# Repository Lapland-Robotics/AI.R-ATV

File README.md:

# AI.R-Autonomous_Robot

This is a modular, ROS2‑based platform designed to streamline the development and deployment of autonomous mobile robots. At its core, it leverages ROS2 Navigation 2 for robust path planning and obstacle avoidance, integrates a flexible sensor suite (Lidar, Stereo camera, Thermal camera, GNSS module, ultrasonic array) for reliable perception, and employs Docker containers to ensure reproducible builds. From low‑level firmware on ESP32 microcontrollers to high‑level controls on an NVIDIA Jetson.

## Directory Tree view
This section outlines the main directory structure of the project, separating documents, firmware, hardware designs, and ROS2-based software to keep development organized and modular.
```

├── Documents           # All the Documents and Diagrams
│   ├── MiniATV         # Documents about mini ATV
│   └── Snower          # Documents about Snower
├── Firmware            # All the Firmware programs (for Micro controllers)
├── Hardware            # Universal PCB Design and implementation
├── README.md           # main README file
└── Software            # ROS2 project for Main Brain(Jetson) of the Robots 

```

## System Overview

## ROS2 Transformation Frame Hierarchy

The robot uses a structured TF (transform) tree to manage spatial relationships between all its components, including sensors, base links, and actuators. This hierarchy ensures that data from various sources—like lidar, camera, and GNSS—can be accurately fused and interpreted in a common coordinate space. The TF tree below visualizes how frames are connected and updated in real time during operation.

## Robot Node & Topic Architecture

The ROS2 system is composed of multiple nodes that communicate through a network of topics to handle various tasks like localization, navigation, perception, and control. Each node is modular and focused on a specific function

This diagram, generated with `rqt_graph`, illustrates the live connections between all ROS2 nodes and topics in the Snower. It shows how sensor publishers (e.g., lidar, camera, GNSS, odometry) feed into processing and filtering nodes, how planners and behavior servers interact via action servers/topics, and how control commands flow down to the motor drivers and micro-ROS bridge on the ESP32. By visualizing the full publisher–subscriber and action-server network, you can more verify how each node is wired into the overall autonomy pipeline.

#### In this video, we are testing the autonomous waypoint navigation and dynamic obstacle avoidance capabilities of the Snower 

Click the thumbnail below to watch the demo video:

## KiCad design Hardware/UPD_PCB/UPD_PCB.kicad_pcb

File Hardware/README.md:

# HARDWARE
This folder contains all hardware-related documentation, schematics, PCB designs, and data collection tools for the autonomous robot system.

# Directory Tree view
This section outlines the structure of the Hardware directory, which contains PCB designs, electrical schematics, component research, data logging utilities, and comprehensive documentation for the robot's power distribution and monitoring systems.

```
├── Data_logging                # Python scripts and Excel files for sensor data collection
├── PCB_research                # Research documentation and testing for PCB components
├── UPD_PCB                     # Universal Power Distribution PCB design files
└── User_Manual-UPD-PCB.pdf     # Comprehensive user manual for the UPD PCB
```
# Universal Power Distribution PCB

Designed and developed by Dries Nuttin

## Introduction

The Universal Power Distribution PCB (UDP-PCB) provides the possibility for quick and easy power distribution in any robotics or electronics project ensuring maximum efficiency. A single battery can provide power to 6 different voltage rails with their respective voltage levels (24V, 19V, 16V, 12V, 12V, 5V). Each stage can supply up to 3.5 Amps continuously with a max voltage input of 60V.

A separate battery output has been provided to allow for a motor driver input equal to the battery voltage, protected by a switchable fuse for easier integration into any project. Each voltage rail (except the battery output) has its own INA219 current/voltage/power sensor that communicates via I²C. The current of the entire system is monitored by an ACS711 HALL sensor which sends out a voltage in relation to the current delivered by the battery. An onboard STS30 digital temperature sensor supplies the user with real-time temperature data to ensure that the PCB/ambient temperature does not reach self-made limits.

### Key Features

- **7 voltage outputs** (BAT+, 24V, 19V, 16V, 12V, 12V, 5V)
- **Single battery input** of 4.3V to 60V max
- **6 different voltages** from 1 battery input
- **±1% voltage level accuracy**
- **3.5 Amps continuous**, with a maximum pulse current of 4.3 Amps
- **Real-time monitoring** of current/voltage/power for 6 voltage rails
- **Real-time HAL current monitoring** of the entire current consumption of the PCB
- **Real-time temperature monitoring**
- **Main system over current fault indicator**
- **Rail supply malfunction indicator**
- **±85% Efficiency** for each buck converter stage
- **BAT+ Fuse protection**
- **Single rail shutdown** that leaves the rest unaffected
- **Over current / temperature protection** on each rail
- **No Over-voltage protection**

> **Note:** V1.0 still has specific repair requirements in place, please consult the repair section of the Hardware/User_Manual-UPD-PCB.pdf to see what needs to be done for newly purchased PCBs.

## Product Specifications

### Absolute Maximum Ratings

| No. | Parameter | Min | Typical | Max | Unit |
|-----|-----------|-----|---------|-----|------|
| 1 | Input voltage (Battery+) | 4.3 | - | 60 | V |
| 2 | Current Battery input (Continuous) |  | 32 |   | A |
| 3 | Current Battery input (1 pulse, 100ms) |   | 100 |   | A |
| 4 | Rail current (Continuous) |   | 3.5 |   | A |
| 5 | Rail current (pulsed, hiccup mode) |   | 6 |   | A |
| 6 | Current usage with no output |   | 54 |   | mA |
| 7 | Thermal shutdown threshold |   | 165 |   | °C |
| 8 | PCB temperature | -40 | 35 | 165 | °C |

> **Warning:** These ratings should not be exceeded, doing so can lead to permanent damage to the PCB or components.

### Pin Configuration

| Label | Function | Description |
|-------|----------|-------------|
| A | Main battery input | 4.2V to 60V |
| B | Fuse | Linked to output E |
| C | ACS711 VIout output | Current sensor output |
| D | I²C output | Sensor communication |
| E | Main battery output | With fuse protection |
| F | 24V output | Regulated 24V rail |
| G | 19V output | Regulated 19V rail |
| H | 16V output | Regulated 16V rail |
| I | 12V_1 output | First 12V rail |
| J | 12V_2 output | Second 12V rail |
| K | 5V output | Regulated 5V rail |

**Color Legend:**
- Red = Power input/output
- Yellow = Sensor output
- Grey = Fuse

### LED Status Indicators

If all LEDs are on = Working as expected

| Label | Function | Meaning if not on |
|-------|----------|-------------------|
| A | Fault for ACS711 HALL current sensor | Overcurrent |
| B | Battery output voltage line | No voltage available |
| C | 24V output voltage line | No voltage available |
| D | 19V output voltage line | No voltage available |
| E | 16V output voltage line | No voltage available |
| F | 12V output voltage line | No voltage available |
| G | 12V output voltage line | No voltage available |
| H | 5V output voltage line | No voltage available |

> **Note:** The described reasons might not be the only reasons that the LED is off. The LED itself might be broken, the voltage might be unstable, a connection might have severed, the LED resistor might have broken. Please test the power supplies with multimeter. If the LED is off, please consult the repair section of the Hardware/User_Manual-UPD-PCB.pdf.

## How to Use

The UPD-PCB can be utilized in any robotics project that is powered by 1 battery. This battery can be plugged into the PCB, which will follow by the indicator LEDs turning on and each stage delivering an output voltage. Screw terminals have been provided for ease of use to attach the necessary voltage lines. The GND is shared between all terminals, meaning you can switch the ground cables between voltage in/outputs even though this is not recommended.

### Integration Checklist

To integrate the UPD-PCB into any robotics project please ensure the following:

- The battery output is correctly plugged into the screw terminal plug on the PCB
- It is recommended to have a battery switch and anti-spark unit before the PCB
- The Fuse is plugged into the PCB if battery output is required
- All LEDs are on
- The output wires have the correct polarity
- If needed, the I²C and VIout connections are plugged into an external MCU unit

### Example Setup

An example of a UPD-PCB plugged in correctly. Note that the LEDs are not on due to the battery being switched off.

As can be seen in the image, the polarity of the wires is ensured and coherent with the silkscreen on the PCB itself. The fuse is in place for, in this specific case, 25A, and the I²C and VIout wires are not connected. If the battery was enabled, the LEDs should light up and the PCB will immediately work without issue.

> **Note:** The sensors do not need to be enabled for the PCB to deliver stable power

> **Warning:** It is not recommended to plug/unplug any wires while the PCB is on. Doing so can result in permanent damage if any of the live wires touch the IC's or a spark is generated.

## Power Delivery

The power delivery for each rail is being supplied by a fine-tuned LMR516x5 buck converter. This buck converter works at 400 kHz (might vary due to the FPM version being utilized in this design). More information can be found in the datasheet of the buck converter itself. Each buck converter has been chosen for its high efficiency, low thermal rise, high power output (3.5A continuous).

### Voltage Setting

The output voltage of each rail is decided using an external resistor. This resistor is visible in the image above where the resistor R3 has a red square surrounding it. If the output voltage needs to be replaced or is not at the desired resistance, please change this resistor.

The desired resistor value can be calculated using this equation. All resistors used are size 0603.

```
Resistor = (Vout - 0.8V) / 0.8V × 10200
```

## Sensor Integration

The UPD-PCB can monitor each individual rail for voltage, current and power usage. This can be done by a single MCU which has to read out 1 I²C bus and read out an ADC voltage signal. By following the steps in this section, you will be able to read out these sensors and use them for any application.

An example of the sensor integration. Here you can see an ESP32 actively reading out both the VIout pin and the I²C line from the entire PCB.

### INA219

All relevant I²C addresses can be found in the table below. These addresses are changeable if the A1 and A0 connections are changed. Please note that the I²C address for the temperature sensor is identical to the 16V line (0x4A), this table below already has the changed I²C address, the change itself can be found in the repair section of the Hardware/User_Manual-UPD-PCB.pdf.

| Voltage | A1 Connection | A0 Connection | I²C Address (Binary) | I²C Address (Hex) |
|---------|---------------|---------------|---------------------|-------------------|
| +24V | GND | GND | 1000000 | 0x40 |
| +19V | GND | +5V | 1000001 | 0x41 |
| +16V | GND | SDA | 1000010 | 0x42 |
| +12V_1 | +5V | GND | 1000100 | 0x44 |
| +12V_2 | +5V | +5V | 1000111 | 0x47 |
| +5V | +5V | SDA | 1000101 | 0x45 |

#### Arduino Code

Programming a MCU to receive INA219 data from the UPD-PCB can be done using the Arduino IDE:

1. Open the Arduino library manager
2. Search for the Adafruit INA219 library and install it
3. With this, one of the examples can be opened and it should be ready to use!
4. Ensure that you are using one of the addresses previously mentioned in order to read out from the correct sensor.

More information regarding the INA219 can be found [here](https://cdn-learn.adafruit.com/downloads/pdf/adafruit-ina219-current-sensor-breakout.pdf).

Example code for selecting the correct address:

```cpp
#include <Wire.h>
#include <Adafruit_INA219.h>

Adafruit_INA219 ina219(0x41); // 0x41 = +19V line

void setup() {
  Serial.begin(9600);
  ina219.begin();
}

void loop() {
  Serial.print("V: "); Serial.print(ina219.getBusVoltage_V());
  Serial.print("V, I: "); Serial.print(ina219.getCurrent_mA());
  Serial.print("mA, P: "); Serial.print(ina219.getPower_mW());
  Serial.println("mW");
  delay(1000);
}
```

### ACS711

The ACS711 is a Hall-effect-based current sensor that outputs an analog voltage proportional to the current passing through the entire system. It can be connected to an MCU's ADC pin to allow for full-system current monitoring.

**Specifications:**
- Output voltage (VIout) at 0A: VCC / 2 = 2.5V
- Sensitivity: ~45 mV per Amp
- Range: 30A

A calculation must be made in the MCU to determine the correct amount of current. Since the baseline for the ACS is half of the supply voltage (5V) and any positive current will simply add 0.045V/A on top of that baseline. If the current goes in reverse (which it should never do) the VIout will go lower.

The following calculation can be made:

```
Current (A) = (Vout - 5V/2) / 0.045V
```

Example code implementation:

```cpp
const int ACS_PIN = 36; // e.g., GPIO36 (ADC1)

void setup() {
  Serial.begin(9600);
}

void loop() {
  int adc = analogRead(ACS_PIN);
  float voltage = adc * 5.0 / 4095.0;
  float current = (voltage - 2.5) / 0.045; // 45mV per Amp
  
  Serial.print("Current: "); Serial.print(current); Serial.println(" A");
  delay(1000);
}
```

> **Note:** The 16V INA219 sensor has the same I²C address as the Temperature sensor before doing any repairs. Ensure that you either follow the steps in the repair section of the Hardware/User_Manual-UPD-PCB.pdf, or don't use the temperature sensor.

> **Best Practice:** The best way to ensure accurate measurement is to read out the 5V line from the INA219 sensor and use that in the calculation for the supply voltage. Replace 5V with the correct voltage measurement.

### STS30

The STS30 is a digital I²C temperature sensor made by Sensirion, known for its high accuracy and reliability. It outputs temperature values in °C directly over the I²C bus.

**Specifications:**
- Communication: I²C
- I²C address: 0x4A
- Accuracy: ±0.2°C
- Range: -40°C to +125°C

To read out the temperature sensor, an Arduino library such as SHT31 can be used to make it easier to read out the temperature sensor.

```cpp
#include <Wire.h>
#include "Adafruit_SHT31.h"

Adafruit_SHT31 sht = Adafruit_SHT31();

void setup() {
  Serial.begin(9600);
}

void loop() {
  float temp = sht.readTemperature();
  if (!isnan(temp)) {
    Serial.print("Temperature: ");
    Serial.print(temp);
    Serial.println(" °C");
  }
  delay(1000);
}
```

### For more information, please refer to the Hardware/User_Manual-UPD-PCB.pdf.

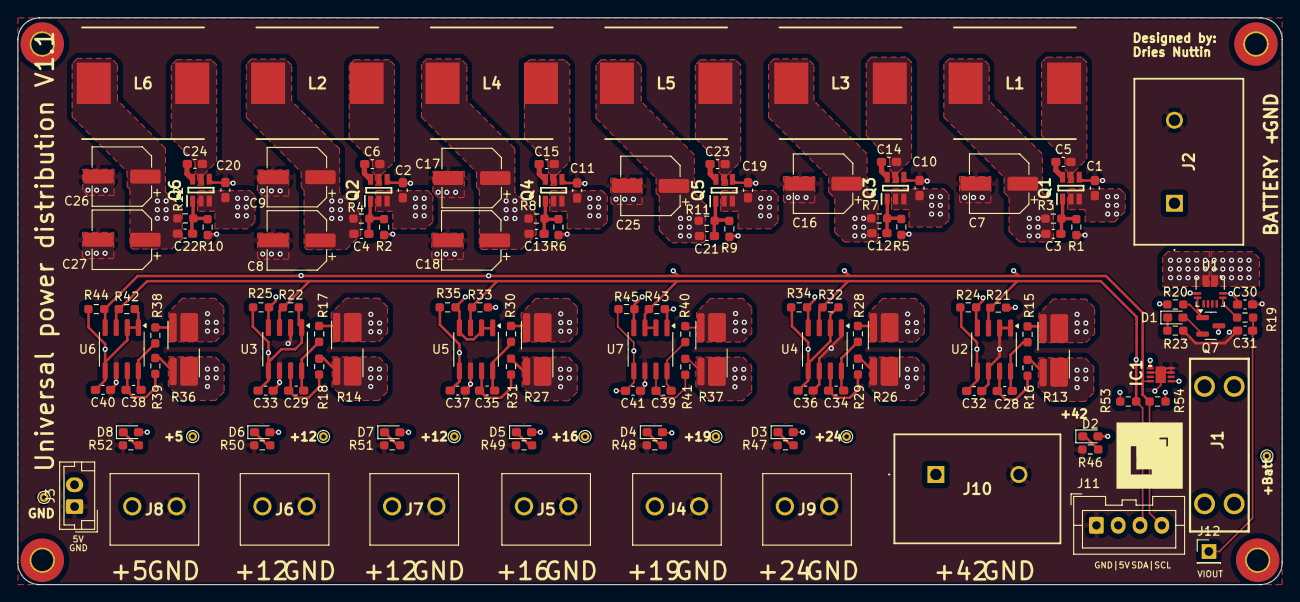
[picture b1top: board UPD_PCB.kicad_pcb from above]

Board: 6 copper layers, 145.0 x 65.0 mm, 144 parts (0 on the bottom side), 60 nets.

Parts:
C1, C2, C10, C11, C19, C20: 2.2µF; C_0603_1608Metric_Pad1.08x0.95mm_HandSolder
C3, C4, C12, C13, C21, C22: DNP; C_0603_1608Metric_Pad1.08x0.95mm_HandSolder
C5, C6, C14, C15, C23, C24, C28, C29, C30, C31, C32, C33, C34, C35, C36, C37, C38, C39, C40, C41: 0.1µF; C_0603_1608Metric_Pad1.08x0.95mm_HandSolder
C7, C9, C16, C18, C25: 22µF; CP_Elec_6.3x5.8
C8, C17: 10µF; CP_Elec_6.3x5.8
C26, C27: 33µF; CP_Elec_6.3x5.8
D1, D2, D3, D4, D5, D6, D7, D8: LED; LED_0603_1608Metric_Pad1.05x0.95mm_HandSolder
IC1: STS30-DIS; SON50P250X250X100-9N-D
J1: 25A Fuse holder; 3557-2
J2, J10: 796739-2; 7967392
J3: Conn_01x02; JST_EH_B2B-EH-A_1x02_P2.50mm_Vertical
J4, J5, J6, J7, J8, J9: 1776119-2; 17761192
J11: Conn_01x04; JST_XA_B04B-XASK-1_1x04_P2.50mm_Vertical
J12: Conn_01x01; PinHeader_1x01_P2.54mm_Vertical
L1, L3, L5: 33µH; INDPM140128X650N
L2, L4: 22µH; INDPM140128X650N
L6: 15µH; INDPM140128X650N
Q1, Q2, Q3, Q4, Q5, Q6: LMR51635XDDCR; SOT95P280X110-6N
Q7: BSS84; SOT-23
R1, R2, R5, R6, R9, R10: 10k2; R_0603_1608Metric_Pad0.98x0.95mm_HandSolder
R3: 295k; R_0603_1608Metric_Pad0.98x0.95mm_HandSolder
R4, R8: 143k; R_0603_1608Metric_Pad0.98x0.95mm_HandSolder
R7: 232k; R_0603_1608Metric_Pad0.98x0.95mm_HandSolder
R11: 194k; R_0603_1608Metric_Pad0.98x0.95mm_HandSolder
R12: 53k5; R_0603_1608Metric_Pad0.98x0.95mm_HandSolder
R13, R14, R26, R27, R36, R37: 0.1R; R_shunt_different_pad_layout
R15, R16, R17, R18, R28, R29, R30, R31, R38, R39, R40, R41: R50; R_0603_1608Metric_Pad0.98x0.95mm_HandSolder
R19: 0R; R_0603_1608Metric_Pad0.98x0.95mm_HandSolder
R20, R50: 1k; R_0603_1608Metric_Pad0.98x0.95mm_HandSolder
R21, R22, R24, R25, R32, R33, R34, R35, R42, R43, R44, R45, R53, R54: 10k; R_0603_1608Metric_Pad0.98x0.95mm_HandSolder
R23, R51, R52: 330; R_0603_1608Metric_Pad0.98x0.95mm_HandSolder
R46: 4k; R_0603_1608Metric_Pad0.98x0.95mm_HandSolder
R47: 2.2k; R_0603_1608Metric_Pad0.98x0.95mm_HandSolder
R48: 1.8k; R_0603_1608Metric_Pad0.98x0.95mm_HandSolder
R49: 1.4k; R_0603_1608Metric_Pad0.98x0.95mm_HandSolder
TP1, TP2, TP3, TP4, TP5, TP6, TP7, TP8: TestPoint; TestPoint_THTPad_D1.0mm_Drill0.5mm
U1: ACS711xEXLT-31AB; Allegro_QFN-12-10-1EP_3x3mm_P0.5mm
U2, U3, U4, U5, U6, U7: INA219AxD; SOIC-8_3.9x4.9mm_P1.27mm

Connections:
+5V_NS: C22.2, C26.1, C27.1, L6.2, R12.1, R36.1, R36.2, R38.1
+5V_out: C30.1, C32.2, C33.2, C36.2, C37.2, C40.2, C41.2, D8.2 (A), IC1.5 (VDD), J3.2, J8.1, J11.2, Q7.3 (D), R20.1, R21.2, R22.2, R24.2, R25.2, R32.2, R33.2, R34.2, R35.2, R36.3, R36.4, R39.1, R42.2, R43.2, R44.2, R45.2, R53.2, R54.2, TP7.1, U1.10 (VCC), U2.5 (VS), U3.1 (A1), U3.5 (VS), U4.2 (A0), U4.5 (VS), U5.5 (VS), U6.1 (A1), U6.2 (A0), U6.5 (VS), U7.1 (A1), U7.5 (VS)
+12V_1: C4.2, C8.1, C9.1, L2.2, R4.1, R14.1, R14.2, R17.1
+12V_1_out: D6.2 (A), J6.1, R14.3, R14.4, R18.1, TP3.1
+12V_2: C13.2, C17.1, C18.1, L4.2, R8.1, R27.1, R27.2, R30.1
+12V_2_out: D7.2 (A), J7.1, R27.3, R27.4, R31.1, TP5.1
+16V: C21.2, C25.1, L5.2, R11.1, R37.1, R37.2, R40.1
+16V_out: D5.2 (A), J5.1, R37.3, R37.4, R41.1, TP6.1
+19V: C12.2, C16.1, L3.2, R7.1, R26.1, R26.2, R28.1
+19V_out: D4.2 (A), J4.1, R26.3, R26.4, R29.1, TP4.1
+24V: C3.2, C7.1, L1.2, R3.1, R13.1, R13.2, R15.1
+24V_out: D3.2 (A), J9.1, R13.3, R13.4, R16.1, TP2.1
+42V: C1.1, C2.1, C10.1, C11.1, C19.1, C20.1, J1.1, J1.3, Q1.2 (EN), Q1.3 (VIN), Q2.2 (EN), Q2.3 (VIN), Q3.2 (EN), Q3.3 (VIN), Q4.2 (EN), Q4.3 (VIN), Q5.2 (EN), Q5.3 (VIN), Q6.2 (EN), Q6.3 (VIN), U1.2 (IP-)
+42V_out: D2.2 (A), J1.2, J1.4, J10.1, TP8.1
GND: C1.2, C2.2, C7.2, C8.2, C9.2, C10.2, C11.2, C16.2, C17.2, C18.2, C19.2, C20.2, C25.2, C26.2, C27.2, C30.2, C31.2, C32.1, C33.1, C36.1, C37.1, C40.1, C41.1, IC1.2 (ADDR), IC1.7 (R), IC1.8 (VSS), IC1.9 (EP), J2.2, J3.1, J4.2, J5.2, J6.2, J7.2, J8.2, J9.2, J10.2, J11.1, Q1.4 (GND), Q2.4 (GND), Q3.4 (GND), Q4.4 (GND), Q5.4 (GND), Q6.4 (GND), R1.2, R2.2, R5.2, R6.2, R9.2, R10.2, R23.2, R46.1, R47.1, R48.1, R49.1, R50.1, R51.1, R52.1, TP1.1, U1.3 (GND), U2.1 (A1), U2.2 (A0), U2.6 (GND), U3.2 (A0), U3.6 (GND), U4.1 (A1), U4.6 (GND), U5.6 (GND), U6.6 (GND), U7.6 (GND)
INA_SCL: IC1.4 (SCL), J11.4, R24.1, R25.1, R34.1, R35.1, R44.1, R45.1, R54.1, U2.4 (SCL), U3.4 (SCL), U4.4 (SCL), U5.1 (A1), U5.2 (A0), U5.4 (SCL), U6.4 (SCL), U7.4 (SCL)
INA_SDA: IC1.1 (SDA), J11.3, R21.1, R22.1, R32.1, R33.1, R42.1, R43.1, R53.1, U2.3 (SDA), U3.3 (SDA), U4.3 (SDA), U5.3 (SDA), U6.3 (SDA), U7.2 (A0), U7.3 (SDA)
IP+: J2.1, U1.1 (IP+)
unnamed: D1.2 (A), Q7.2 (S)
unnamed: D1.1 (K), R23.1
unnamed: D2.1 (K), R46.2
unnamed: D3.1 (K), R47.2
unnamed: D4.1 (K), R48.2
unnamed: D5.1 (K), R49.2
unnamed: D6.1 (K), R50.2
unnamed: D7.1 (K), R51.2
unnamed: D8.1 (K), R52.2
unnamed: C5.1, Q1.6 (CB)
unnamed: C3.1, Q1.1 (FB), R1.1, R3.2
unnamed: C5.2, L1.1, Q1.5 (SW)
unnamed: C6.1, Q2.6 (CB)
unnamed: C4.1, Q2.1 (FB), R2.1, R4.2
unnamed: C6.2, L2.1, Q2.5 (SW)
unnamed: C14.1, Q3.6 (CB)
unnamed: C12.1, Q3.1 (FB), R5.1, R7.2
unnamed: C14.2, L3.1, Q3.5 (SW)
unnamed: C15.1, Q4.6 (CB)
unnamed: C13.1, Q4.1 (FB), R6.1, R8.2
unnamed: C15.2, L4.1, Q4.5 (SW)
unnamed: C23.1, Q5.6 (CB)
unnamed: C21.1, Q5.1 (FB), R9.1, R11.2
unnamed: C23.2, L5.1, Q5.5 (SW)
unnamed: C24.1, Q6.6 (CB)
unnamed: C22.1, Q6.1 (FB), R10.1, R12.2
unnamed: C24.2, L6.1, Q6.5 (SW)
unnamed: Q7.1 (G), R20.2, U1.4 (~FAULT)
unnamed: R19.1, U1.9 (VIOUT)
unnamed: C28.1, R15.2, U2.8 (IN+)
unnamed: C28.2, R16.2, U2.7 (IN-)
unnamed: C29.1, R17.2, U3.8 (IN+)
unnamed: C29.2, R18.2, U3.7 (IN-)
unnamed: C34.1, R28.2, U4.8 (IN+)
unnamed: C34.2, R29.2, U4.7 (IN-)
unnamed: C35.1, R30.2, U5.8 (IN+)
unnamed: C35.2, R31.2, U5.7 (IN-)
unnamed: C38.1, R38.2, U6.8 (IN+)
unnamed: C38.2, R39.2, U6.7 (IN-)
unnamed: C39.1, R40.2, U7.8 (IN+)
unnamed: C39.2, R41.2, U7.7 (IN-)
VIOUT: C31.1, J12.1, R19.2

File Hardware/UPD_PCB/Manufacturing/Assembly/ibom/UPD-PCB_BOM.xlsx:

| Type | Quantity | Manufaturer number | Manufacturer | Description | Value | Part on PCB
 | Capacitor | 6 | GRM188R61H225ME11D | Murata | Multilayer Ceramic Capacitors MLCC | 2.2uF | C1,C2,C10,C11,C19,C20
 | Capacitor | 20 | CGA3E3X7S2A104M080AB | TDK | Multilayer Ceramic Capacitors MLCC | 0.1uF | C5,C6,C14,C15,C23,C24,C28,C29,C30,C31,C32,C33,C34,C35,C36,C37,C38,C39,C40,C41
 | Capacitor | 5 | UCD1V220MCL1GS | Nichicon | Aluminium Electrolytic Capacitors | 22uF | C7,C9,C16,C18,C25
 | Capacitor | 2 | UCD1V100MCL1GS | Nichicon | Aluminium Electrolytic Capacitors | 10uF | C8,C17
 | Capacitor | 2 | UCD1V330MCL1GS | Nichicon | Aluminium Electrolytic Capacitors | 33uF | C26,C27
 | LED | 8 | KT EELP41.12-S2U1-25-2X4X-5-R18 | ams OSRAM | Single Colour LEDs | - | D1,D2,D3,D4,D5,D6,D7,D8
 | IC | 1 | STS30-DIS | Sensirion | Board Mount Temperature Sensors | - | IC1
 | IC | 1 | LMR51635XDDCR | Texas Instruments | Switching Voltage Regulators synchronous buck convert | - | Q1,Q2,Q3,Q4,Q5,Q6
 | IC | 1 | INA219AIDR | Texas Instruments | INA219 Current and power monitor | - | U2,U3,U4,U5,U6,U7
 | IC | 1 | ACS711KEXLT-31AB-T | Allegro MicroSystems | ACS711 Hall current sensor | - | U1
 | Mosfet | 1 | BSS84 | onsemi | MOSFETs SOT-23 P-CH ENHANCE | - | Q7
 | Inductor | 3 | PA4343.333NLT | Pulse | Power Inductors | 33uH 8A | L1,L3,L5
 | Inductor | 2 | PA4343.223NLT | Pulse | Power Inductors | 22uH 9A | L2,L4
 | Inductor | 1 | PA4343.153NLT | Pulse | Power Inductors | 15uH 9A | L6
 | Shunt Resistor | 6 | WSL2512R1000FEA | Vishay | Current Sense Resistors | 0.1R | R13,R14,R26,R27,R36,R37
 | Resistor | 6 | CRCW060310K2FKEAHP | Vishay | Thick Film Resistor 0603 | 10.2K | R1,R2,R5,R6,R9,R10
 | Resistor | 1 | CRCW0603294KFKEA | Vishay | Thick Film Resistor 0603 | 294K | R3
 | Resistor | 2 | CRCW0603143KFKEA | Vishay | Thick Film Resistor 0603 | 143K | R4,R8
 | Resistor | 1 | CRCW0603232KFKEA | Vishay | Thick Film Resistor 0603 | 232K | R7
 | Resistor | 1 | CRCW0603196KFKEA | Vishay | Thick Film Resistor 0603 | 196K | R11
 | Resistor | 1 | CRCW060353K6FKEAC | Vishay | Thick Film Resistor 0603 | 53.6K | R12
 | Resistor | 12 | CRCW060350R0FKEA | Vishay | Thick Film Resistor 0603 | 50R | R15,R16,R17,R18,R28,R29,R30,R31,R38,R39,R40,R41
 | Resistor | 1 | CRCW06030000Z0ED | Vishay | Thick Film Resistor 0603 | 0R | R19
 | Resistor | 2 | CRCW06031K00FKED | Vishay | Thick Film Resistor 0603 | 1.00K | R20, R52
 | Resistor | 14 | CRCW060310K0FKEE | Vishay | Thick Film Resistor 0603 | 10.0K | R21,R22,R24,R25,R32,R33,R34,R35,R42,R43,R44,R45,R53,R54
 | Resistor | 1 | CRCW0603330RFKEA | Vishay | Thick Film Resistor 0603 | 330R | R23
 | Resistor | 1 | CRCW06032K40FKEA | Vishay | Thick Film Resistor 0603 | 2.4K | R51,R50
 | Resistor | 1 | CRCW06033K24FKEA | Vishay | Thick Film Resistor 0603 | 3.2K | R49
 | Resistor | 1 | CRCW06033K83FKEA | Vishay | Thick Film Resistor 0603 | 3.8K | R48
 | Resistor | 1 | CRCW06034K87FKEA | Vishay | Thick Film Resistor 0603 | 4.8K | R47
 | Resistor | 1 | CRCW06038K45FKEA | Vishay | Thick Film Resistor 0603 | 8.4K | R46
 | Connector | 1 | 3557-2 | Keystone Electronics | Fuse Holder 2 IN 1 FUSE HOLDER | - | J1
 | Connector | 2 | 796739-2 | TE Connectivity | Fixed Terminal Blocks 2P SIDE ENTRY 9.52mm | - | J2,J10
 | Connector | 6 | 1776119-2 | TE Connectivity | Fixed Terminal Blocks 2P SIDE ENTRY 5.08mm | - | J4,J5,J6,J7,J8,J9
 | Connector | 1 | 114020163 | Seeed Studio | Seeed Studio Accessories SMD Grove Female Header-Beige | - | J11

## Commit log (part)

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2024-05-27 gitignore
2024-05-27 init
2024-05-27 speed feedback demo
2024-05-27 Docker ADD
2024-05-28 ESP32 code
2024-07-01 init - tested code from miniATV for ROS1
2024-07-01 Modified the directory structure
2024-07-01 Modified README.md files
2024-07-03 code refactor 1
2024-07-03 code refactor 2 and debug function
2024-07-04 code refactor 3
2024-07-04 code refactor 4
2024-07-04 code refactor 5 and Simulation
2024-07-05 code refactor 6
2024-07-10 US_9479: init ROS2
2024-07-10 US_9479: ROS2 microros stable
2024-07-11 US_9479: ESP32TimerInterrupt lib update to 2.3.0 version
2024-07-12 fixed the Interrupt issue
2024-07-12 Boards Manager version
2024-07-14 US_9479: microros serial communication & docker composer
2024-07-15 US_9479: update Jetson README.md
2024-07-15 US_9479: modified /atv/debug to String data type
2024-07-16 US_9479: Twist msg Control Command Subscription
2024-07-17 US_9479: Control Command publisher and testing
2024-07-17 US_9479: steering safty limits
2024-07-23 US_9479: ROS2 migration complete and tested
2024-07-23 US_9479: documents
2024-07-24 US_9481: init commit
2024-07-31 Update ESP32.ino
    Space allocation might be wrong since I'm not sure if twist.data.data exists. twist.data.size and twist.data.capacity should exist.
2024-08-01 new some line codes for switch
2024-08-07 9485: Enhance potentiometer mechanism
2024-08-07 9496: Update the ESP32 readme file
2024-08-08 9481: Auto and RC mode switch tested
2024-08-09 US_9481: code refactor
2024-08-12 US_9546: code Refactor with struct + getters & setters
2024-08-12 US_9546: struct CtrlRequest data hiding
2024-08-13 US_9546: ModeSwitchPin modification and code refactor
2024-08-13 US_9546: fix all the compiler warning messages
2024-08-23 US_9546: refactor
2024-09-10 US_9546: ultrasonic
2024-09-13 US_9804: newPing lib
2024-09-13 US_9813: init ZED-F9P ESP32 code
2024-10-04 snower electrical diagram
2024-10-04 US_9813: GNSS ros2 publisher impl
2024-10-09 US_9813: gnss microros
2024-10-11 US_9813: GNSS debug topic
2024-10-11 US_9813: GNSS debug and gps topic
2024-10-14 US_9813: Refactor, DDS port open and speed limit change
2024-10-14 directory restructure
2024-10-14 README.md update
2024-10-14 test
2024-10-15 doc: directory restructure
2024-10-15 US_9804: Safety_SW_State
2024-10-15 doc: restructure
2024-10-15 orginal code from git@github.com:Lapland-Robotics/Snower.git
2024-10-15 Revert "orginal code from git@github.com:Lapland-Robotics/Snower.git"
    This reverts commit 325acb6d8a0b97e119af45c9bdc82bc61b1464fa.
2024-10-16 US_10388: Teensy -> ESP32
2024-10-16 US_10388: refactor
2024-10-16 US_10388: snower microros
2024-10-17 US_10388: snower microros 2
2024-10-18 US_10388: snower RC bug fix
2024-10-18 US_10388: multi docker container microservice arch
2024-10-21 US_10388: systemd services
2024-10-21 US_10388: created systemd services
2024-10-22 Add ESP32 pinout image and diagram
2024-10-24 US_10388: ouster_lidar container service
2024-10-24 US_10388: ouster_lidar_ws path
2024-10-25 US_10388: /snower/gps -> /snower/gnss
2024-10-25 US_10388: memory
2024-10-26 US_10388: fix [ros2run] std::bad_alloc issue
2024-10-29 US_10388: motor controller safty switch and power saving ft
2024-11-11 US_10658: store data zed2 camara topic & new run.launch.py to execute multiples nodes
2024-11-12 US_10658: genarate folders using timestamp and save images inside the genarated folder
2024-11-13 US_10658: on demand subcribers for multiple topics
2024-11-24 minor parameter changes
2024-11-25 US_10512: change save location /app/ATV/Dataset -> /srv/ATV/Dataset
2024-11-25 US_10512: bug fix
2024-11-25 US_10512: thermal image and todo note
2024-11-26 US_10825: deactivating data_collector node for general branches
2024-11-26 US_10825: urdf, map -> odom and odom -> base_link tf
2024-11-26 US_10825: odom publisher
2024-11-27 US_10825: QoS ReliabilityPolicy.BEST_EFFORT
2024-11-27 US_10825: urdf modifications
2024-11-27 US_10825: docker multicast and unicast port mapping
2024-11-27 US_10825: udrf modification
2024-12-05 US_10825: odom modifications
2024-12-11 US_10512: Seek Thermal publisher
2024-12-11 seek thermal camara numpy issue
2024-12-17 bushbutton code is added
2024-12-18 US_10512: seek thermal camara impl completed
2025-01-07 US_10825: improve the /robot_description
2025-01-07 US_10825: added the collisions for xacro files
2025-01-07 US_10825: formatted xacro files
2025-01-07 US_10825: odom modification
2025-02-04 US_10825: zed2 camara link
2025-02-06 US_10825: ekf odom implementation
2025-02-06 US_10825: ros-humble-robot-localization
2025-02-07 US_10825: robot-localization parameter for imu
2025-02-09 US_10825: upgraded to cyclonedds
2025-02-11 universal pcb diagram
2025-02-12 Speed sensor mount and code
2025-02-12 code for LiDar is done.
2025-02-13 Speed sensor integration
    Added the speed sensors to the esp32
2025-02-17 added project for universal power distribution pcb
2025-02-17 Added initial design
2025-02-18 Updated snower code
2025-02-18 microcontroller code updated
2025-02-24 US_11439: init
2025-02-24 US_10512: wireless trigger button
2025-02-25 Updated universal PCB
2025-02-25 finalized schematic 1
2025-02-26 Updated pcb, added feedback resistors
2025-02-26 US_11361: speed pulluppins and general block
2025-02-26 debug motor pwm
2025-02-26 US_11361: loop delay removed and added timer blocks
2025-02-27 US_11361: /speed/left debug
2025-02-27 US_11361: Serial.print() while microros running
2025-02-27 US_11361: README updated
2025-02-27 US_11361: pullup pins changed
2025-02-28 Restructured pcb
2025-03-01 US_11361: cmd_vel and cmd_vel request strut modification for left and right wheel speed
2025-03-01 US_11361: code refactor
2025-03-02 US_11361: code refactor and bug fix
2025-03-03 US_11439: bug fix
2025-03-03 US_10512: disable cyclonedds
2025-03-04 US_10512: change the topic of the stero camara
2025-03-04 US_10512: bgra8 support
2025-03-05 US_11439: config modification
2025-03-05 US_10512: wireless trigger switch error loop
2025-03-05 Updated project architecture
    Changed the entire project layout to be more professional
2025-03-05 Changed text variables
2025-03-07 Updated schematic
2025-03-08 US_10512: folder naming and code refactor
2025-03-08 US_10512: backup com wifi
2025-03-08 US_10512: enable cyclonedds
2025-03-08 US_10512: delete unnecessary files
2025-03-08 US_11361: undo docker edits
2025-03-08 US_11606: code refactor
2025-03-08 Updated design
2025-03-10 Updated schematic (before INA219 integration)
2025-03-10 US_11606: wheel_odom_publisher
2025-03-10 Finalized Schematic
2025-03-10 US_11606: speed calibration
2025-03-11 US_11606: bug fix
2025-03-11 First board layout
2025-03-13 Pcb layout before changing inductor
2025-03-13 Routed main traces
2025-03-13 Updated pcb
2025-03-14 Final pcb before review
2025-03-18 Finalized PCB
2025-03-19 Finalized pcb
    Connector still needs to be changed
2025-03-19 Final PCB design
2025-03-20 Finalized version V1.0
2025-03-20 11606: Wheel Odometry - Snower
2025-03-20 US_11756: gitignore
2025-03-20 US_11756: base_footprint
2025-03-20 US_11756: nev2 related configurations
2025-03-24 Dual speed sensor code
2025-03-27 US_11760: atv -> robot
2025-03-27 US_11760: updated README.md and rename .service files
2025-03-27 US_11760: pkg robot, data_collector and navigator
2025-04-09 US_11760: Navigator launch file
2025-04-10 Added INA219 instructions
2025-04-10 US_11760: parameter and config modification
2025-04-10 US_11760: Navigator config
2025-04-11 US_11760: Systemctl files
2025-04-11 US_11760: Autonomous Navigation disable auto activation
2025-04-11 US_11760: rviz update
2025-04-14 US_11760: snower.yaml modifications
2025-04-16 US_11760: snower-ros2-docker.service
2025-04-16 US_11760: systemctl services
2025-04-19 US_11760: fix the costmap issue and added the laser odom to robot_localization
2025-04-28 Version 1.1 of PCB
2025-04-29 US_11760: ESP32 improvements
2025-04-29 US_11760: slamtool box param file
2025-05-05 US_12222: set -e for systemctls
2025-05-05 US_12222: pointcloud to laserscan
2025-05-05 US_12222: Add auto-restart for Micro-ROS speed sensor on failure
2025-05-09 Full system monitoring of PCB
2025-05-12 US_12222: ros config bash file
2025-05-13 US_12222: cyclone dds xml
2025-05-13 US_12222: cyclone dds config
2025-05-13 US_12222: cyclone dds config stable version 1
2025-05-13 US_12222: cyclone dds config stable version 2
2025-05-14 12222: configure cyclone dds config xml to docker file
2025-05-14 US_12222: cyclone dds config stable version 3
2025-05-14 US_12222: optimize the thermal camara publisher
2025-05-14 US_12222: delete unnesssory files
2025-05-25 US_12426: init zenoh config
2025-05-25 documentation: tf_tree and rqt_graph
2025-05-25 documentation: update
2025-05-25 documentation: Software README update
2025-05-27 Finalization
2025-05-30 Final push
2025-06-09 US_12426: zenoh config tested
2025-06-10 US_12426: zenoh docker cofig
2025-06-16 US_12426: zenoh config modifications
2025-06-16 US_12426: zenoh cofig
2025-06-17 US_12426: ouster lidar zenoh docker
2025-06-17 US_12426: ouster_lidar service
2025-06-18 US_13059: add ouster and zed driver as sub modules
2025-06-18 US_13059: submodule update
2025-06-23 US_13059: repo path var
2025-06-23 US_13059: repo path var modification in bash scripts
2025-06-23 US_13059: system configuration correction
2025-06-23 US_13059: bug fix
2025-06-23 US_13059: ouster docker
2025-06-24 US_13059: docker improv
2025-06-24 US_13059: dockerfile improv
2025-06-24 US_13059: docker container for zed camara
2025-06-24 US_13059: zed docker improv
2025-06-24 US_13059: monitor sensor rviz
2025-06-25 US_12426: magnatic speed sensor esp32
2025-06-26 US_8909: speed sensor change - 1
2025-06-26 US_8909: speed sensor change - 2
2025-06-26 US_13059: submodule status
2025-07-01 US_8909 : Speed sensor changes
    Now using PCNT driver (pulse counter)
2025-07-02 Revert "US_12426: magnatic speed sensor esp32"
    This reverts commit 97bb13792b873b255f6eca8fc71b53b1af6b4dd7.
2025-07-02 Zenoh: zenoh specific configurations and cleanup
2025-07-02 Zenoh: cleanup
2025-07-02 US_13162: Init code
2025-07-03 US_13162: gpu usage
2025-07-03 US_13162: snower nav2 config
2025-07-04 US_13162: snower nav2 configurations and wheel odom
2025-07-04 US_13162: wheel odom topic and firmware modifications
2025-07-07 US_13162: ResourceMonitorNode
2025-07-08 US_13162: navigation, slam and wheel odometry modifications
2025-07-14 US_13162 : Localization, navigation, acml and slam modification. Added scan filtering
2025-07-24 US_13162 : Localisation and navigations modifications. Implementation of MPPI controller
2025-07-24 US_13162 : Implementation of bias corrector for zed imu. Changed robot package configuration to use cpp and python
2025-07-24 US_13162 : Changed rviz navigation configuration to show navigation waypoints (MarkerArray)
2025-07-25 US_13162: README updated
2025-08-01 US_13162: README files updated
2025-08-04 US_13207 : Changed snower firmware project from Arduino IDE to PlatformIO IDE
2025-08-05 US_13162 : IMU bias correction updated
2025-08-06 documentation: Power Distribution PCB README.md
2025-08-06 Documentation : minor change in README.md
2025-08-06 Documentation : Added design and stl files of motor support and gears for the mini-ATV
    .f3d files are for Fusion360 if you need to change the designs
    .stl and .step are for 3D printing or manufacturing
2025-08-06 US_13251: init cicd pipeline
2025-08-06 US_13251: added a missing CMakeList.txt file
2025-08-06 US_13251: complete basic github ci pipeline
2025-08-07 US_13251: build from dockerfile
2025-08-07 US_13251: added 2 jobs
2025-08-07 US_13251: microros test
2025-08-07 US_13251: ci pipeline
2025-08-07 Create LICENSE
2025-08-07 Update LICENSE
    Lapland UAS
2025-08-08 US_13207 : Changed zedf9p_esp32 project from Arduino IDE to platformIO IDE
2025-08-08 US_13207: init Ultrasonic project to platfomIO
2025-08-08 US_13207: added the lib and removed the arduino ide project
2025-08-11 US_13207 : Changed MiniATV project from Arduino IDE to PlatformIO IDE
2025-08-11 US_13251 : Added job to build firmware
2025-08-11 US_13251 : Firmware CI test
2025-08-12 US_13251: remove the test branch tag
2025-08-14 Update LICENSE
